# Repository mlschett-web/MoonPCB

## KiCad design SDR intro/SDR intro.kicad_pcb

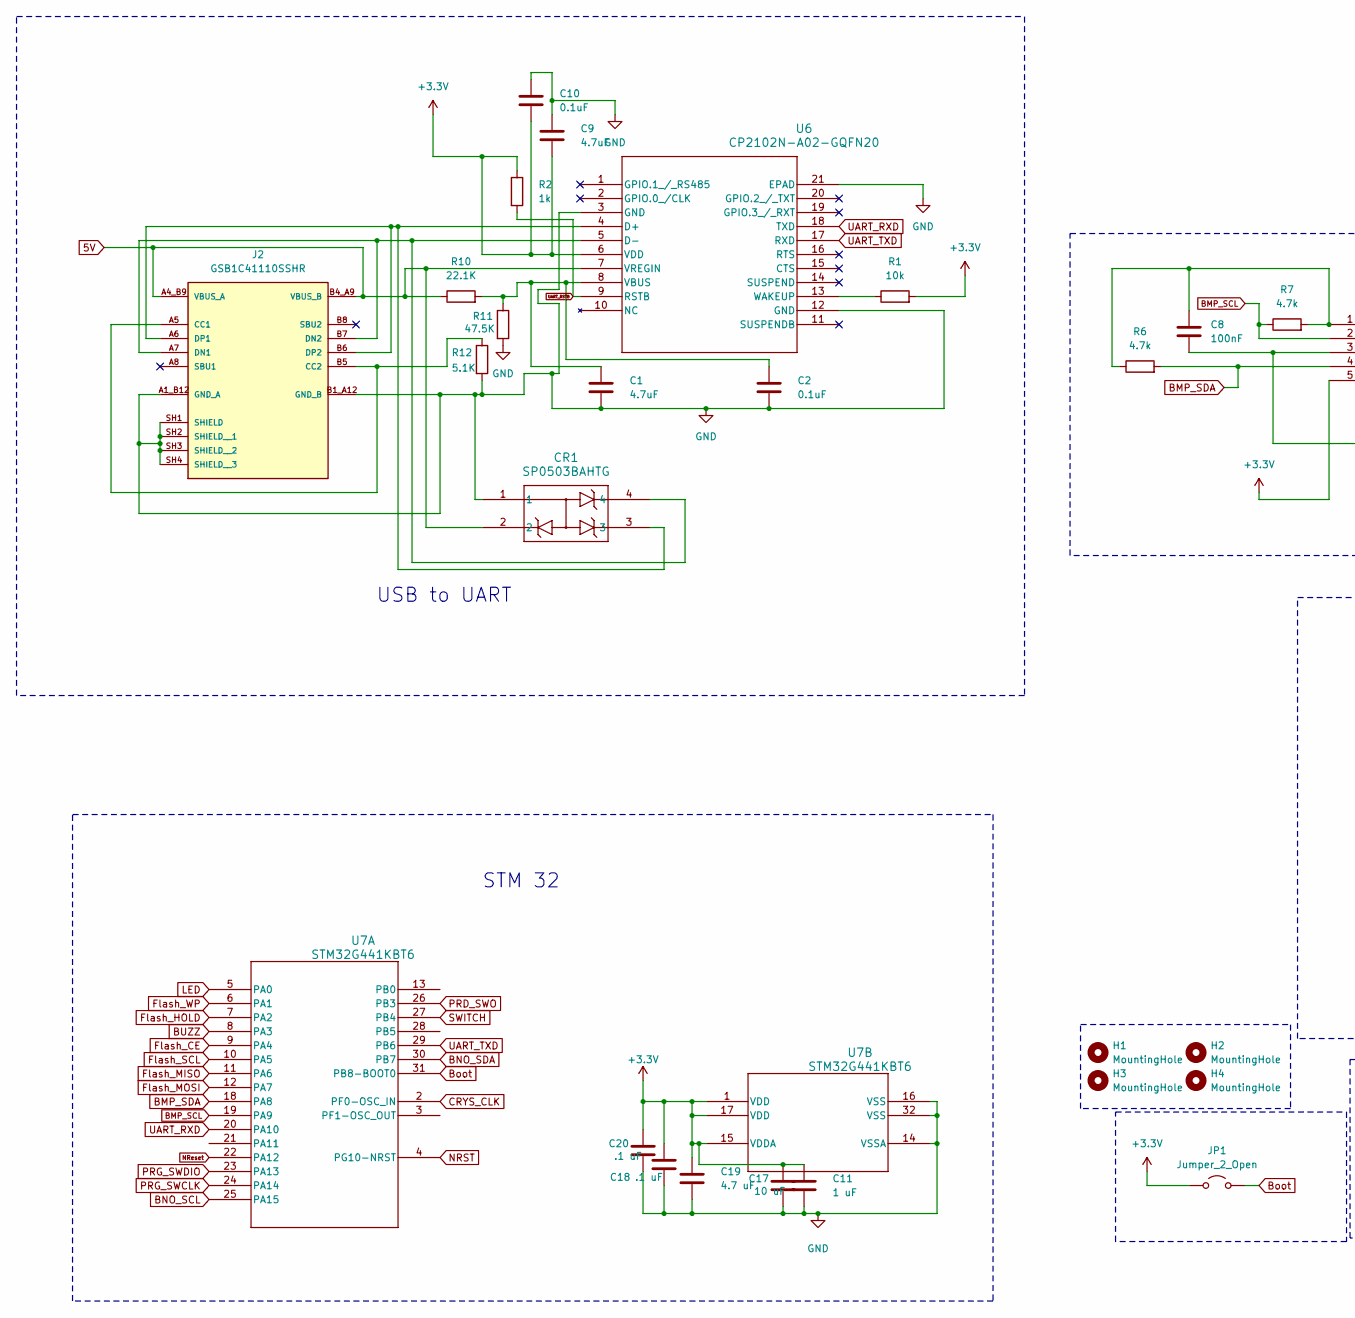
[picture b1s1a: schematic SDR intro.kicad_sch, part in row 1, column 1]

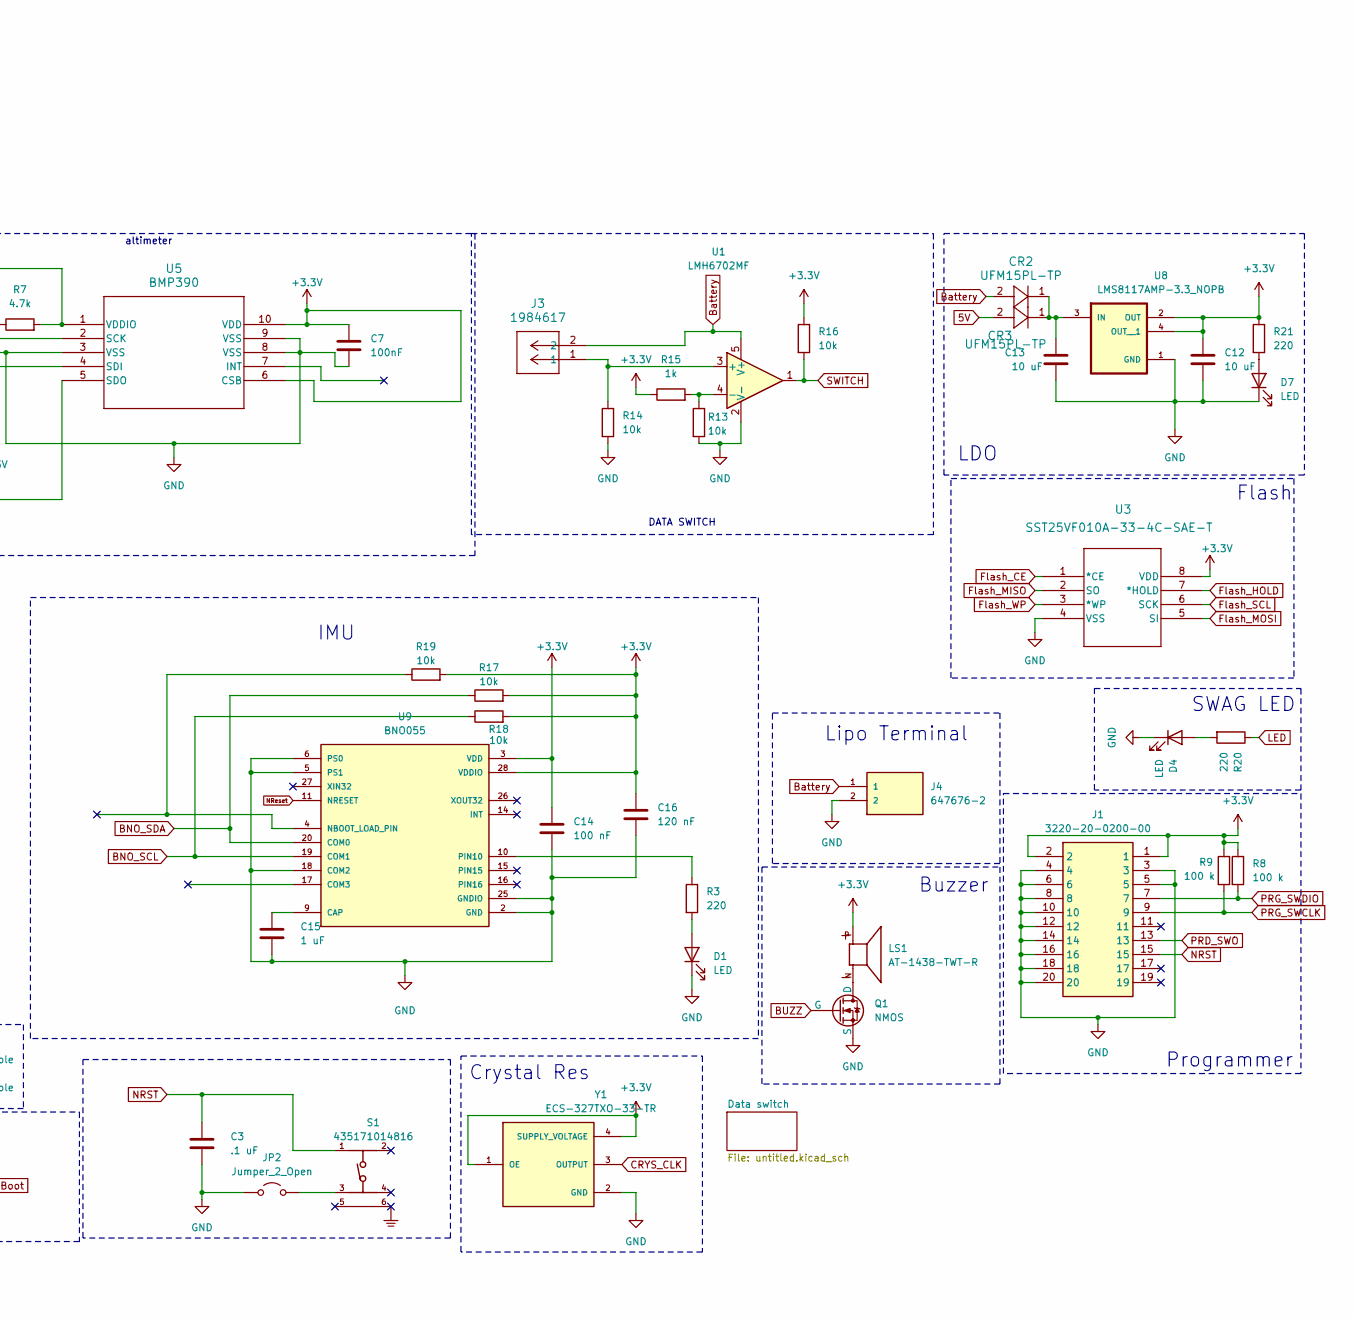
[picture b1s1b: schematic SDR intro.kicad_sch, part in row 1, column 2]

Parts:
C1, C9: 4.7uF; C_0603_1608Metric
C2, C10: 0.1uF; C_0603_1608Metric
C3, C18, C20: .1 uF; C_0603_1608Metric
C7, C8: 100nF; C_0603_1608Metric
C11, C15: 1 uF; C_0603_1608Metric
C12, C13, C17: 10 uF; C_0603_1608Metric
C14: 100 nF; C_0603_1608Metric
C16: 120 nF; C_0603_1608Metric
C19: 4.7 uF; C_0603_1608Metric
CR1: SP0503BAHTG; SOT-143
CR2, CR3: UFM15PL-TP; SOD-123FL_MCC
D1, D4, D7: LED; LED_0603_1608Metric
H1, H2, H3, H4: MountingHole; MountingHole_2.2mm_M2
J1: 3220-20-0200-00; 322020020000; Manufacturer_Part_Number 3220-20-0200-00
J2: GSB1C41110SSHR; AMPHENOL_GSB1C41110SSHR; PARTREV AX1
J3: 1984617; CONN_1984617_PXC
J4: 647676-2; TE_647676-2; PARTREV R
JP1, JP2: Jumper_2_Open; R_0603_1608Metric
LS1: AT-1438-TWT-R; XDCR_AT-1438-TWT-R; PARTREV H
Q1: NMOS; TSOT-23
R1, R13, R14, R16, R17, R18, R19: 10k; R_0603_1608Metric
R2, R15: 1k; R_0603_1608Metric
R3, R20, R21: 220; R_0603_1608Metric
R6, R7: 4.7k; R_0603_1608Metric
R8, R9: 100 k; R_0603_1608Metric
R10: 22.1K; R_0603_1608Metric
R11: 47.5K; R_0603_1608Metric
R12: 5.1K; R_0603_1608Metric
S1: 435171014816
U1: LMH6702MF; SOT-23-5
U3: SST25VF010A-33-4C-SAE-T; SOIC8_SA_SST_MCH
U5: BMP390; 10LGA_2X2X0p75_BOS
U6: CP2102N-A02-GQFN20; QFN20_CP2102N_SIL
U7: STM32G441KBT6; LQFP-32
U8: LMS8117AMP-3.3_NOPB; SOT230P700X180-4N
U9: BNO055; LGA28R50P4X10_380X520X100
Y1: ECS-327TXO-33-TR; OSC_ECS-327TXO-33-TR; PARTREV Rev.2019

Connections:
5V: CR1.2, CR3.2, J2.A4_B9 (VBUS_A), J2.B4_A9 (VBUS_B), R10.1, U6.7 (VREGIN)
+3.3V: C7.1, C9.2, C10.2, C11.1, C12.1, C14.1, C16.1, C17.1, C18.1, C19.1, C20.1, J1.1, J1.2, JP1.1 (A), LS1.P, R1.2, R2.1, R8.1, R9.1, R15.1, R16.1, R17.2, R18.2, R19.2, R21.1, U3.8 (VDD), U5.5 (SDO), U5.6 (CSB), U5.10 (VDD), U6.6 (VDD), U7.1 (VDD), U7.15 (VDDA), U7.17 (VDD), U8.2 (OUT), U8.4 (OUT__1), U9.3 (VDD), U9.28 (VDDIO), Y1.1 (OE), Y1.4 (SUPPLY_VOLTAGE)
BMP_SCL: R7.1, U5.2 (SCK), U7.19 (PA9)
BMP_SDA: R6.2, U5.4 (SDI), U7.18 (PA8)
BNO_SCL: R18.1, U7.25 (PA15), U9.19 (COM1)
BNO_SDA: R17.1, U7.30 (PB7), U9.20 (COM0)
BUZZ: Q1.2 (G), U7.8 (PA3)
Battery: CR2.2, J3.2, J4.1, U1.5 (V+)
Boot: JP1.2 (B), U7.31 (PB8-BOOT0)
CRYS_CLK: U7.2 (PF0-OSC_IN), Y1.3 (OUTPUT)
Flash_CE: U3.1 (*CE), U7.9 (PA4)
Flash_HOLD: U3.7 (*HOLD), U7.7 (PA2)
Flash_MISO: U3.2 (SO), U7.11 (PA6)
Flash_MOSI: U3.5 (SI), U7.12 (PA7)
Flash_SCL: U3.6 (SCK), U7.10 (PA5)
Flash_WP: U3.3 (*WP), U7.6 (PA1)
GND: C1.2, C2.2, C3.2, C7.2, C8.2, C9.1, C10.1, C11.2, C12.2, C13.2, C14.2, C15.2, C16.2, C17.2, C18.2, C19.2, C20.2, CR1.1, D1.1 (K), D4.1 (K), D7.1 (K), J1.3, J1.4, J1.5, J1.6, J1.8, J1.10, J1.12, J1.14, J1.16, J1.18, J1.20, J2.A1_B12 (GND_A), J2.B1_A12 (GND_B), J2.SH1 (SHIELD), J2.SH2 (SHIELD__1), J2.SH3 (SHIELD__2), J2.SH4 (SHIELD__3), J4.2, JP2.1 (A), Q1.3 (S), R11.2, R12.2, R13.2, R14.2, U1.2 (V-), U3.4 (VSS), U5.3 (VSS), U5.8 (VSS), U5.9 (VSS), U6.3 (GND), U6.12 (GND), U6.21 (EPAD), U7.14 (VSSA), U7.16 (VSS), U7.32 (VSS), U8.1 (GND), U9.2 (GND), U9.5 (PS1), U9.6 (PS0), U9.18 (COM2), U9.25 (GNDIO), Y1.2 (GND)
LED: R20.1, U7.5 (PA0)
NRST: C3.1, J1.15, S1.1, U7.4 (PG10-NRST)
NReset: U7.22 (PA12), U9.11 (NRESET)
unnamed: D1.2 (A), R3.2
unnamed: D4.2 (A), R20.2
unnamed: D7.2 (A), R21.2
unnamed: J2.A5 (CC1), J2.B5 (CC2), R12.1
unnamed: CR1.4, J2.A7 (DN1), J2.B7 (DN2), U6.5 (D-)
unnamed: CR1.3, J2.A6 (DP1), J2.B6 (DP2), U6.4 (D+)
unnamed: JP2.2 (B), S1.3
unnamed: LS1.N, Q1.1 (D)
unnamed: J3.1, R14.1, U1.3 (+)
unnamed: R13.1, R15.2, U1.4 (-)
unnamed: C8.1, R6.1, R7.2, U5.1 (VDDIO)
unnamed: C1.1, C2.1, R10.2, R11.1, U6.8 (VBUS)
unnamed: R1.1, U6.13 (WAKEUP)
unnamed: C13.1, CR2.1, CR3.1, U8.3 (IN)
unnamed: C15.1, U9.9 (CAP)
unnamed: R3.1, U9.10 (PIN10)
PRD_SWO: J1.13, U7.26 (PB3)
PRG_SWCLK: J1.9, R9.2, U7.24 (PA14)
PRG_SWDIO: J1.7, R8.2, U7.23 (PA13)
SWITCH: R16.2, U1.1, U7.27 (PB4)
UART_RSTB: R2.2, U6.9 (RSTB)
UART_RXD: U6.18 (TXD), U7.20 (PA10)
UART_TXD: U6.17 (RXD), U7.29 (PB6)

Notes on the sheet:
Crystal Res
SWAG LED
Flash
Lipo Terminal
LDO
Buzzer
DATA SWITCH
STM 32
USB to UART
IMU
Programmer
altimeter

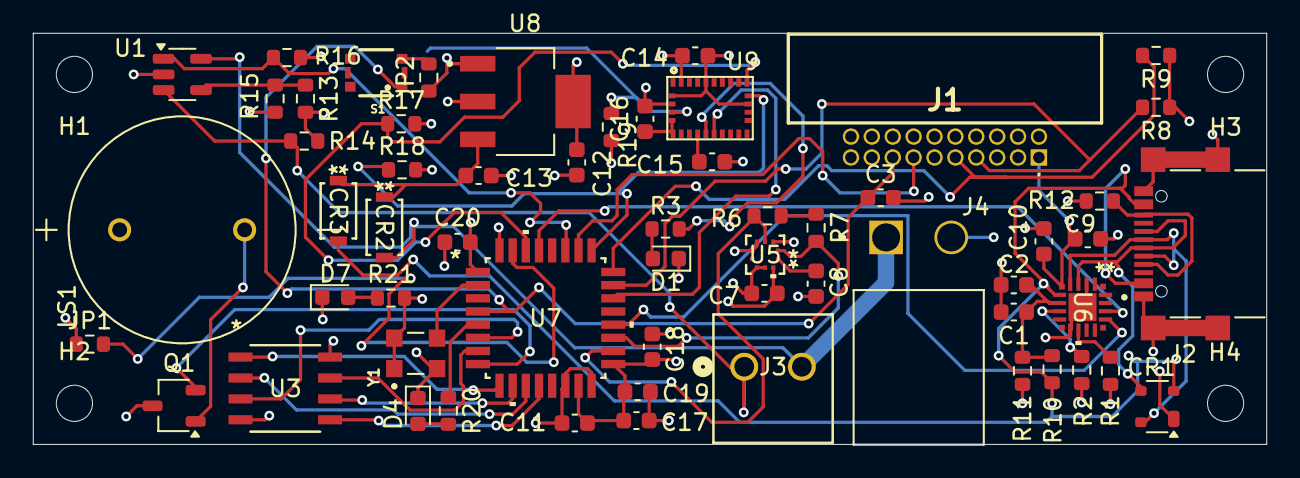
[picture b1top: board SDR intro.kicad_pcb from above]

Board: 4 copper layers, 75.0 x 25.0 mm, 63 parts (0 on the bottom side), 43 nets.

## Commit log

2026-02-13 fuck patrick for baming me flop ball
